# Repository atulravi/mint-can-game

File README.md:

# mint-can-game
ch32 powered mint can game

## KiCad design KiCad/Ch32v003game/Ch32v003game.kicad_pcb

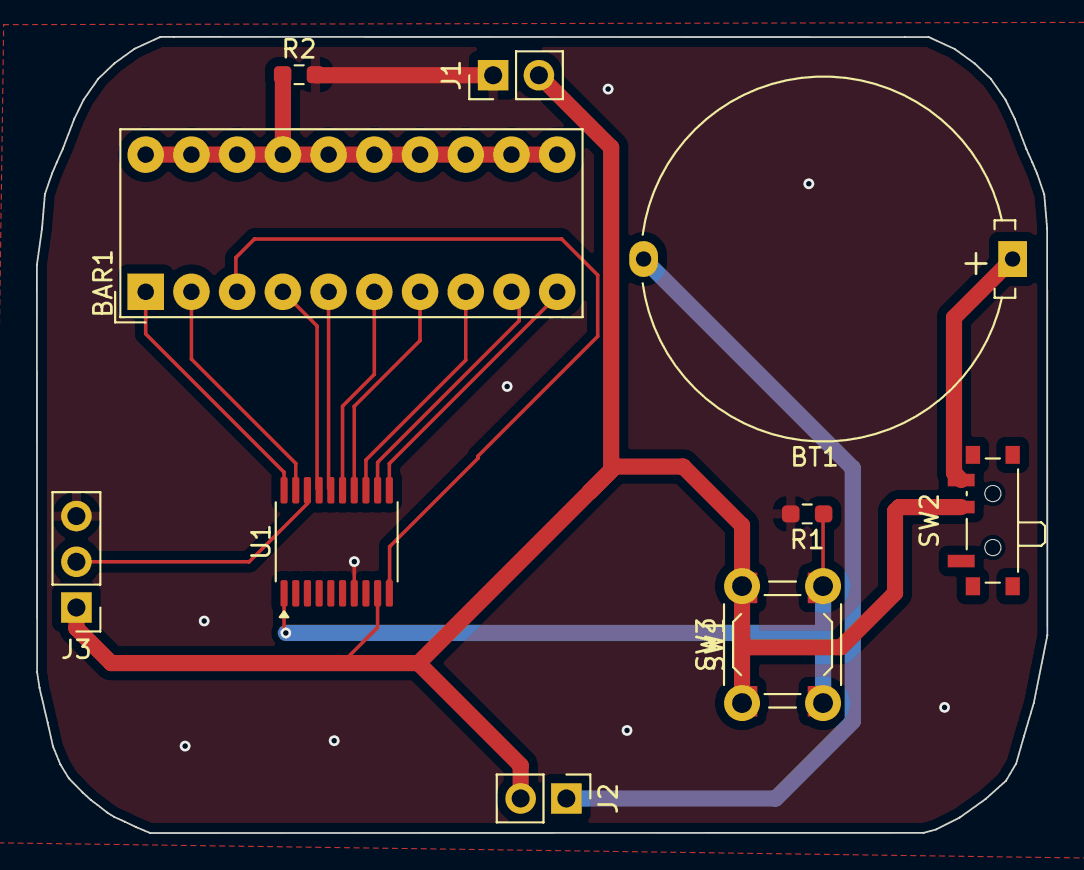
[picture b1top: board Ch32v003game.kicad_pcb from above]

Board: 2 copper layers, 56.1 x 44.2 mm, 11 parts (0 on the bottom side), 17 nets.

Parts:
BAR1: HDSP-4830_2; HDSP-4830
BT1: Battery_Cell; Battery_Panasonic_CR2032-HFN_Horizontal_CircularHoles
J1, J2: Conn_01x02_Socket; PinHeader_1x02_P2.54mm_Vertical
J3: Conn_01x03_Socket; PinHeader_1x03_P2.54mm_Vertical
R1, R2: R; R_0603_1608Metric_Pad0.98x0.95mm_HandSolder
SW1: SW_DPST; SW_SPST_TL3342
SW2: SW_SPDT; SW_SPDT_PCM12
SW3: SW_DPST; SW_PUSH_6mm
U1: CH32V003FxPx; TSSOP-20_4.4x6.5mm_P0.65mm

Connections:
/PC0: BAR1.3 (A), U1.10 (PC0)
/PC1: BAR1.10 (A), U1.11 (PC1)
/PC2: BAR1.9 (A), U1.12 (PC2)
/PC3: BAR1.8 (A), U1.13 (PC3)
/PC4: BAR1.7 (A), U1.14 (PC4)
/PC5: BAR1.6 (A), U1.15 (PC5)
/PC6: BAR1.5 (A), U1.16 (PC6)
/PC7: BAR1.4 (A), U1.17 (PC7)
/PD2: BAR1.2 (A), U1.19 (PD2)
/PD3: BAR1.1 (A), U1.20 (PD3)
/SW: R1.1, SW1.2, SW3.2, U1.1 (PD4)
/SWD: J3.2, U1.18 (PD1)
GND: J1.1, J3.3, R1.2, R2.2, U1.7 (VSS)
unnamed: BAR1.11 (K), BAR1.12 (K), BAR1.13 (K), BAR1.14 (K), BAR1.15 (K), BAR1.16 (K), BAR1.17 (K), BAR1.18 (K), BAR1.19 (K), BAR1.20 (K), R2.1
unnamed: BT1.1 (+), SW2.3 (C)
unnamed: BT1.2 (-), J2.1
VCC: J1.2, J2.2, J3.1, SW1.1, SW2.2 (B), SW3.1, U1.9 (VDD)

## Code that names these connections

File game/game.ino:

const int numLeds = 10;  
int ledPins[numLeds] = {PC1, PC2, PC3, PC4, PC5, PC6, PC7,PC0 , PD2, PD3}; 
const int buttonPin = PD4; 
const int buzzerPin = PD5;  
int targetLed;   
int randomseedinitializer = 9;         
int buttonState = LOW;     

int ledIndex = 0;         
int delayTime = 100;     


int randomTargetLed() {
  randomSeed(randomseedinitializer);
  
  randomseedinitializer--;
  if (randomseedinitializer == 0) {
      randomseedinitializer = numLeds-1; 
  }
  return random(0, numLeds-1);  
}


void displayTargetLed() {
  //First set all LEDs to LOW
  for (int i = 0; i < numLeds; i++) {
        digitalWrite(ledPins[i], LOW);
  }
  //Set the TargetLED alone high
  digitalWrite(ledPins[targetLed], HIGH); 
 }

void setup() {
  for (int i = 0; i < numLeds; i++) {
    pinMode(ledPins[i], OUTPUT);
  }
  pinMode(buttonPin, INPUT); 
  pinMode(buzzerPin, OUTPUT); 

  
  targetLed = randomTargetLed(); 
  Serial.begin(9600);             

  displayTargetLed();  
}

void loop() {

  for (int i = 0; i < numLeds; i++) {
    if ( i != targetLed)
      digitalWrite(ledPins[i], LOW);
  }

  digitalWrite(ledPins[ledIndex], HIGH);

  buttonState = digitalRead(buttonPin);

  
  if (buttonState == HIGH) {
    
    if (ledIndex == targetLed) {
      
      for (int i = 0; i < numLeds; i++) {
          digitalWrite(ledPins[i], HIGH);
      }
      delay(1500);  
     
      targetLed = randomTargetLed(); 
      displayTargetLed();            
      buttonState == LOW;
    } else {
      delay(500);  
    }
  }

  ledIndex++;
  
  if (ledIndex >= numLeds) {
    ledIndex = 0; 
  }
 
  delay(delayTime); 
}
